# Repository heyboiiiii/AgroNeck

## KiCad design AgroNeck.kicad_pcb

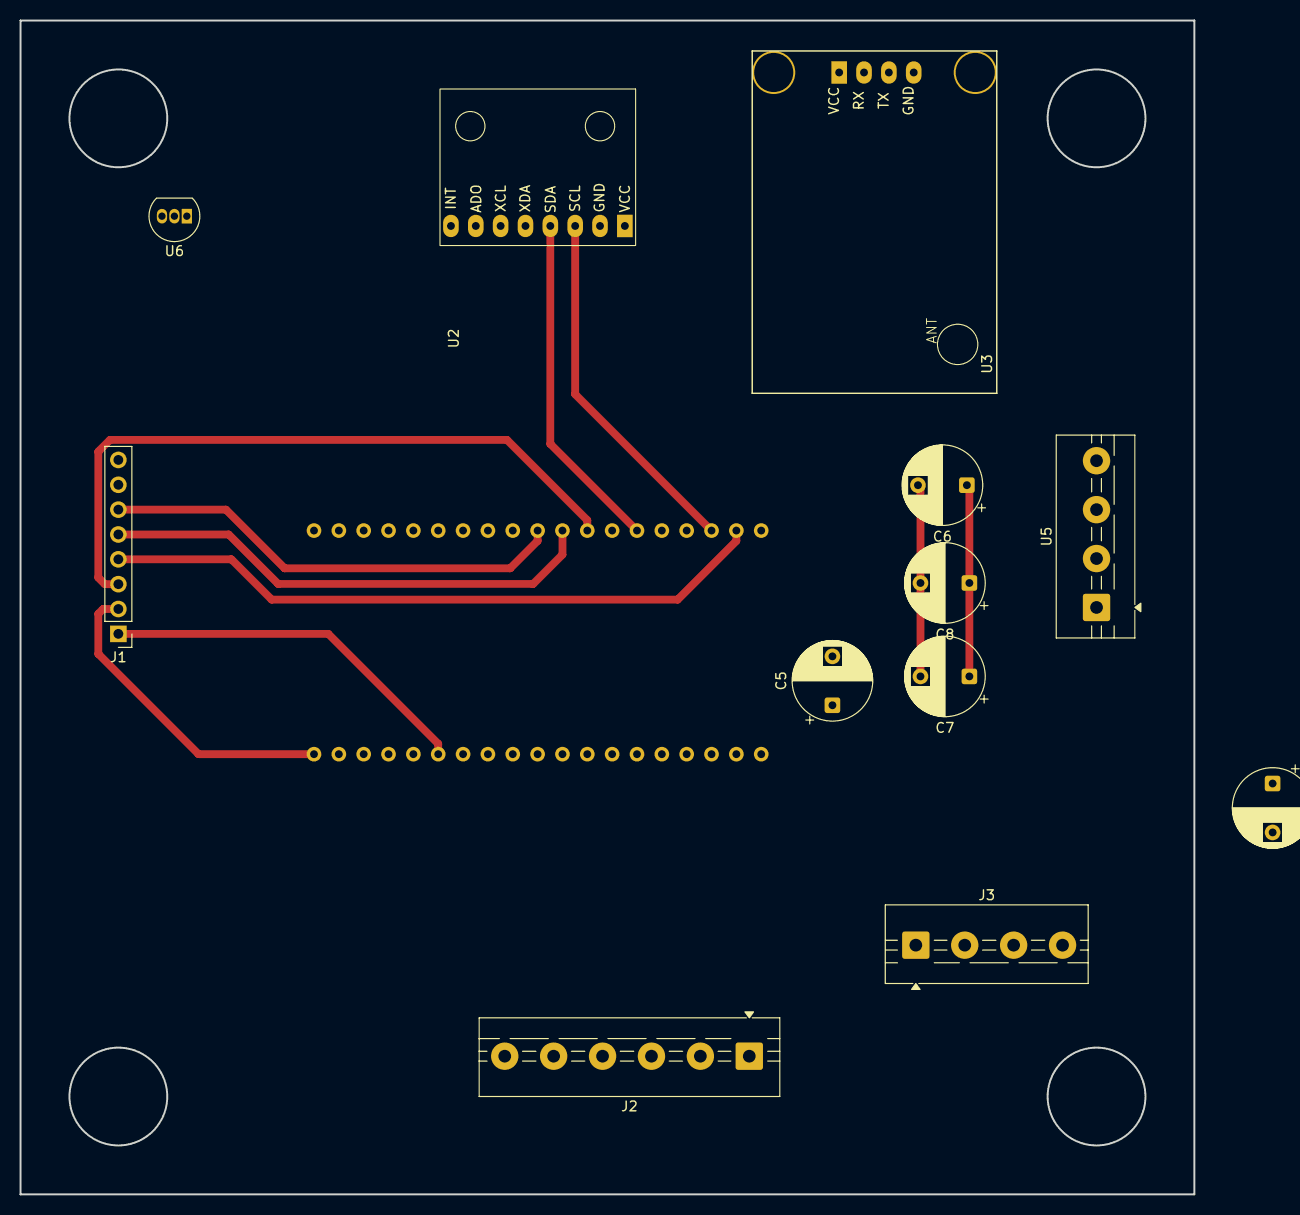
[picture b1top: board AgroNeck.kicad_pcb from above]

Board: 2 copper layers, 120.0 x 120.0 mm, 13 parts (0 on the bottom side), 21 nets.

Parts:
C4, C6: 100uF; CP_Radial_D8.0mm_P5.00mm
C5: 1uF; CP_Radial_D8.0mm_P5.00mm
C7: 0.1uF; CP_Radial_D8.0mm_P5.00mm
C8: 470uF; CP_Radial_D8.0mm_P5.00mm
J1: Screw_Terminal_01x08; PinHeader_1x08_P2.54mm_Vertical
J2: CONTROLVCC; TerminalBlock_MaiXu_MX126-5.0-06P_1x06_P5.00mm
J3: Screw_Terminal_01x04; TerminalBlock_MaiXu_MX126-5.0-04P_1x04_P5.00mm
U2: MPU6050
U3: GY-NEO6MV2
U5: TerminalBlock_MaiXu_MX126-5.0-04P_1x04_P5.00mm
U6: LM35-LP; TO-92_Inline
U8: ESP32_devkit1

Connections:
+3V3: C5.1, C6.1, C7.1, C8.1, J3.1, U8.1 (3.3V)
CONTROL1: J2.1, U8.7 (GPIO32)
CONTROL2: J2.2, U8.8 (GPIO33)
CONTROL3: J2.3, U8.9 (GPIO25)
CONTROL4: J2.4, U8.10 (GPIO26)
GND: C4.1, C6.2, C7.2, C8.2, J1.1, J2.6, J3.2, J3.4, U2.2 (GND), U3.4 (GND), U5.2 (GND), U6.3 (GND), U8.14 (GND), U8.20 (GND), U8.26 (GND)
LORA_CLK: J1.5, U8.28 (GPIO18)
LORA_CS: J1.6, U8.29 (GPIO5)
LORA_DIO0: J1.7, U8.17 (GPIO13)
LORA_MISO: J1.3, U8.27 (GPIO19)
LORA_MOSI: J1.4, U8.21 (GPIO23)
LORA_RESET: J1.8, U8.12 (GPIO14)
MLX_MPU6050_SCL: U2.3 (SCL), U5.3 (SCL), U8.22 (GPIO22)
MLX_MPU6050_SDA: U2.4 (SDA), U5.4 (SDA), U8.25 (GPIO21)
MPU6050_INT: U2.8 (INT), U8.11 (GPIO27)
NEO6M_RX: U3.2 (RX), U8.31 (GPIO16)
NEO6M_TX: U3.3 (TX), U8.30 (GPIO17)
unnamed: C5.2, U8.2 (EN)
PIEZOELECTRICO_OUT: J3.3, U8.6 (GPIO35)
VCC: C4.2, J1.2, J2.5, U2.1 (VCC), U3.1 (VCC), U5.1 (VIN), U6.1 (+V_{S}), U8.19 (VIN)
V_LM35: U6.2 (V_{OUT}), U8.5 (GPIO34)

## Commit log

2026-05-19 Eliminar y omitir archivos de respaldo de KiCad
2026-05-19 remove old files
2026-05-19 eliminate old files
2026-06-02 actulizado sin pcb
2026-06-04 last version(incomplete)
